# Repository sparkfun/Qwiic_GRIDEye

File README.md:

SparkFun Qwiic Panasonic Grid-EYE Infrared Array AMG88xx
========================================

[*SparkFun Grid-EYE Infrared Array Breakout - AMG8833 (Qwiic) (SEN-14607)*](https://www.sparkfun.com/products/14607)

The GridEYE from Panasonic is a 8 by 8 thermopile array. This means you have an array of 64 pixels each capable of detecting temperature remotely. It’s like having thermal camera (or Predator’s vision) just in really low resolution. The SparkFun Grid-EYE Qwiic carrier board utilizes the high performance, high gain 3.3V AMG88 sensor. Do not hook 5V to this beast! Better yet, use the Qwiic system - it makes it much easier and quicker to get started.

The SparkFun carrier board incorporates all the needed passive components as well as a jumper to change the I2C address and a jumper to remove the pull up resistors if needed.

Repository Contents
-------------------

* **/Documents** - Datasheets
* **/Hardware** - Eagle design files (.brd, .sch)

Documentation
--------------
* **[Arduino Library](https://github.com/sparkfun/SparkFun_GridEYE_Arduino_Library)** - Library for reading the sensor and outputing fun graphics over the serial port
* **[Hookup Guide](https://learn.sparkfun.com/tutorials/qwiic-grid-eye-infrared-array-amg88xx-hookup-guide)** - Basic hookup guide for the Qwiic GRID-Eye Infrared Array.

Product Versions
----------------
* [SEN-14607](https://www.sparkfun.com/products/14607)- SparkFun breakout board for Grid-EYE AMG8833
* [SPX-14568](https://www.sparkfun.com/products/14568)- SparkX breakout board for Grid-EYE AMG8833

License Information
-------------------

This product is _**open source**_! 

Please review the LICENSE.md file for license information. 

If you have any questions or concerns on licensing, please contact techsupport@sparkfun.com.

Please use, reuse, and modify these files as you see fit. Please maintain attribution to SparkFun Electronics and release anyThing Development Board derivative under the same license.

Distributed as-is; no warranty is given.

- Your friends at SparkFun.

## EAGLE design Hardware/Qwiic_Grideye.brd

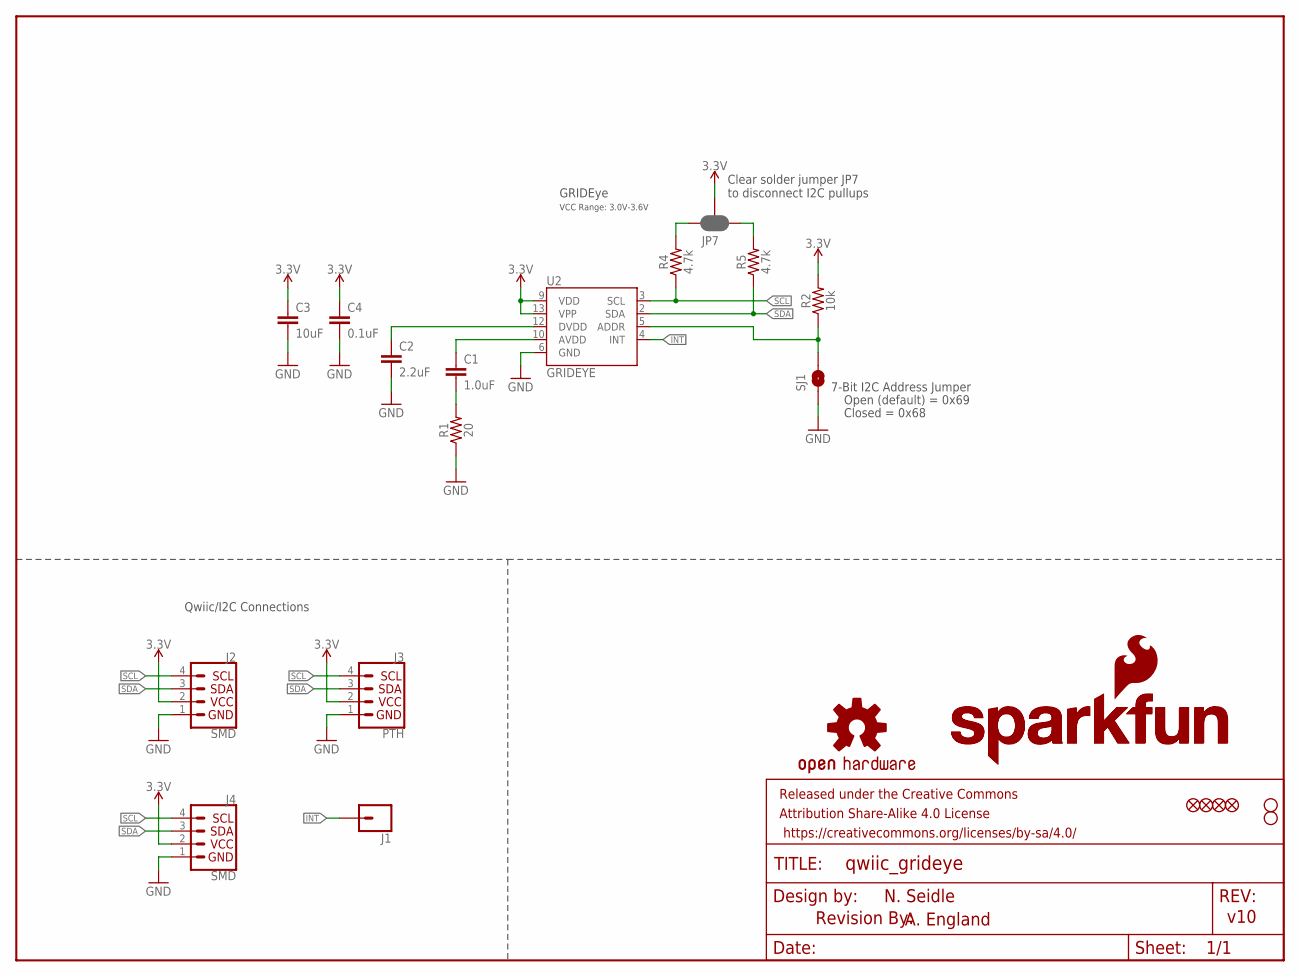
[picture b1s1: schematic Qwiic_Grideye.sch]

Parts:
C1: 1.0uF; 0603
C2: 2.2uF; 0603
C3: 10uF; 0603
C4: 0.1uF; 0603
FRAME1: FRAME-LETTER; CREATIVE_COMMONS
J1: CONN_01PTH_NO_SILK_YES_STOP; 1X01_NO_SILK
J2, J4: SMD; 1X04_1MM_RA
J3: PTH; 1X04_NO_SILK
JP1, JP2, JP5, JP6: FIDUCIALUFIDUCIAL; MICRO-FIDUCIAL
JP3, JP4: STAND-OFF
JP7: JUMPER-SMT_3_2-NC_PASTE_SILK; SMT-JUMPER_3_2-NC_PASTE_SILK
LOGO1: OSHW-LOGOMINI; OSHW-LOGO-MINI
LOGO2: REVISION
R1: 20; 0603
R2: 10k; 0603
R4, R5: 4.7k; 0603
SJ1: SOLDERJUMPERNO; SJ_2S-NO
U2: GRIDEYE; GRIDEYE-AMG88
U$1: SFE_LOGO_NAME.1_INCH; SFE_LOGO_NAME_.1
U$2: SFE_LOGO_NAME_FLAME.1_INCH; SFE_LOGO_NAME_FLAME_.1

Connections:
3.3V: C3.1, C4.1, J2.2 (VCC), J3.2 (VCC), J4.2 (VCC), JP7.2, R2.2, U2.9 (VDD), U2.13 (VPP)
ADDR: R2.1, SJ1.2, U2.5 (ADDR)
GND: C2.2, C3.2, C4.2, J2.1 (GND), J3.1 (GND), J4.1 (GND), R1.1, SJ1.1, U2.6 (GND)
INT: J1.1, U2.4 (INT)
unnamed: JP7.1, R5.2
unnamed: JP7.3, R4.2
unnamed: C2.1, U2.12 (DVDD)
unnamed: C1.1, U2.10 (AVDD)
unnamed: C1.2, R1.2
SCL: J2.4 (SCL), J3.4 (SCL), J4.4 (SCL), R4.1, U2.3 (SCL)
SDA: J2.3 (SDA), J3.3 (SDA), J4.3 (SDA), R5.1, U2.2 (SDA)

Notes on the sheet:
7-Bit I2C Address Jumper
Closed = 0x68
Open (default) = 0x69
N. Seidle
v10
GRIDEye
Clear solder jumper JP7 to disconnect I2C pullups
Qwiic/I2C Connections
A. England
VCC Range: 3.0V-3.6V

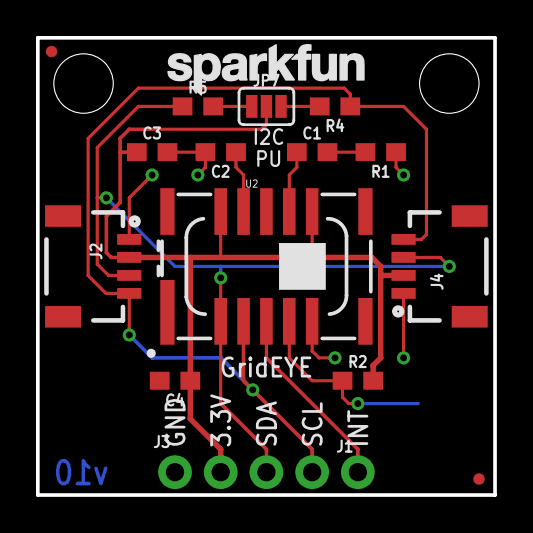
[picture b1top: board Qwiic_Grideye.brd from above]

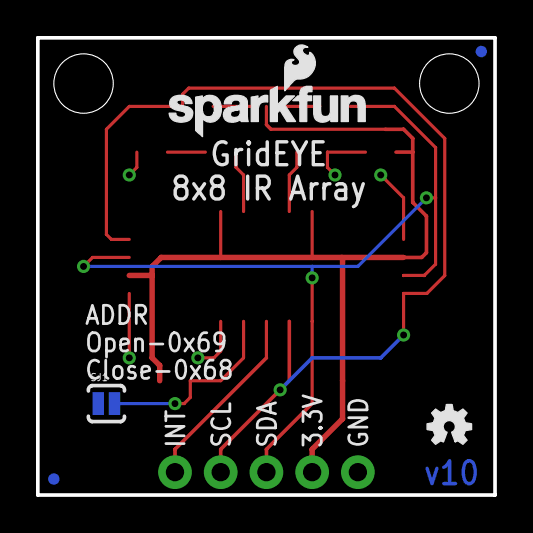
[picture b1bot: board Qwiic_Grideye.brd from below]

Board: 2 copper layers, 25.4 x 25.4 mm, 26 parts (5 on the bottom side), 11 nets.

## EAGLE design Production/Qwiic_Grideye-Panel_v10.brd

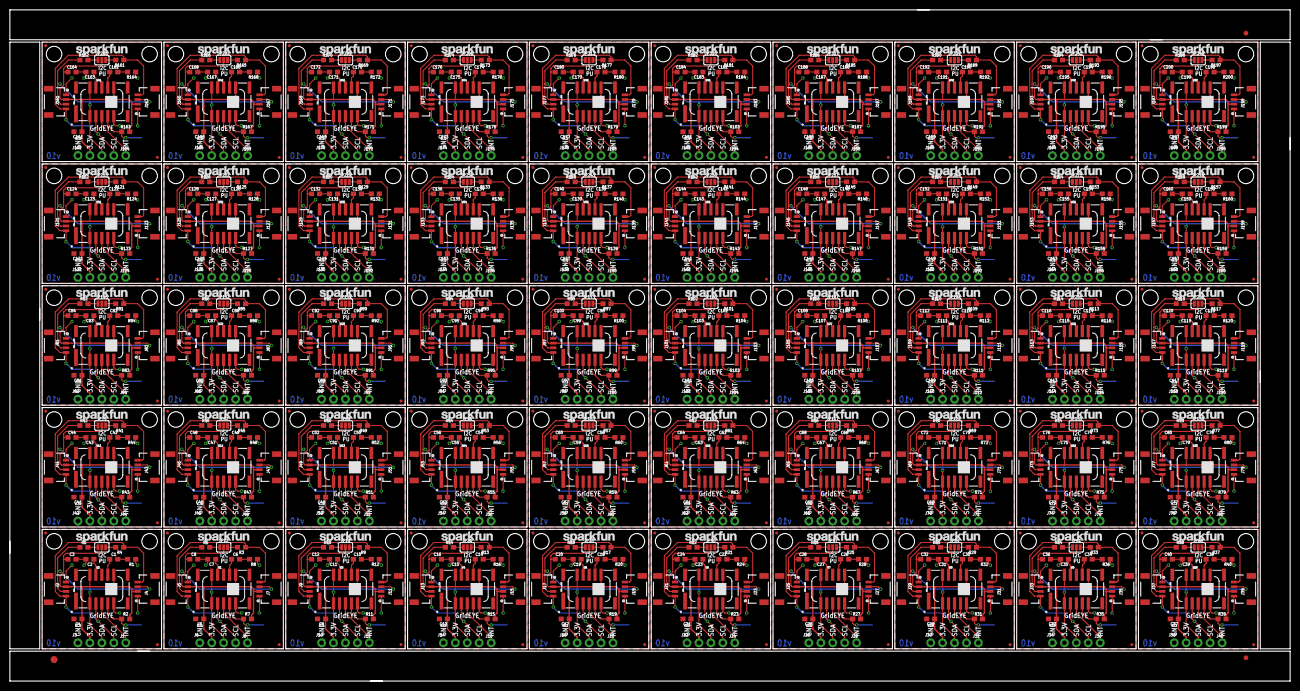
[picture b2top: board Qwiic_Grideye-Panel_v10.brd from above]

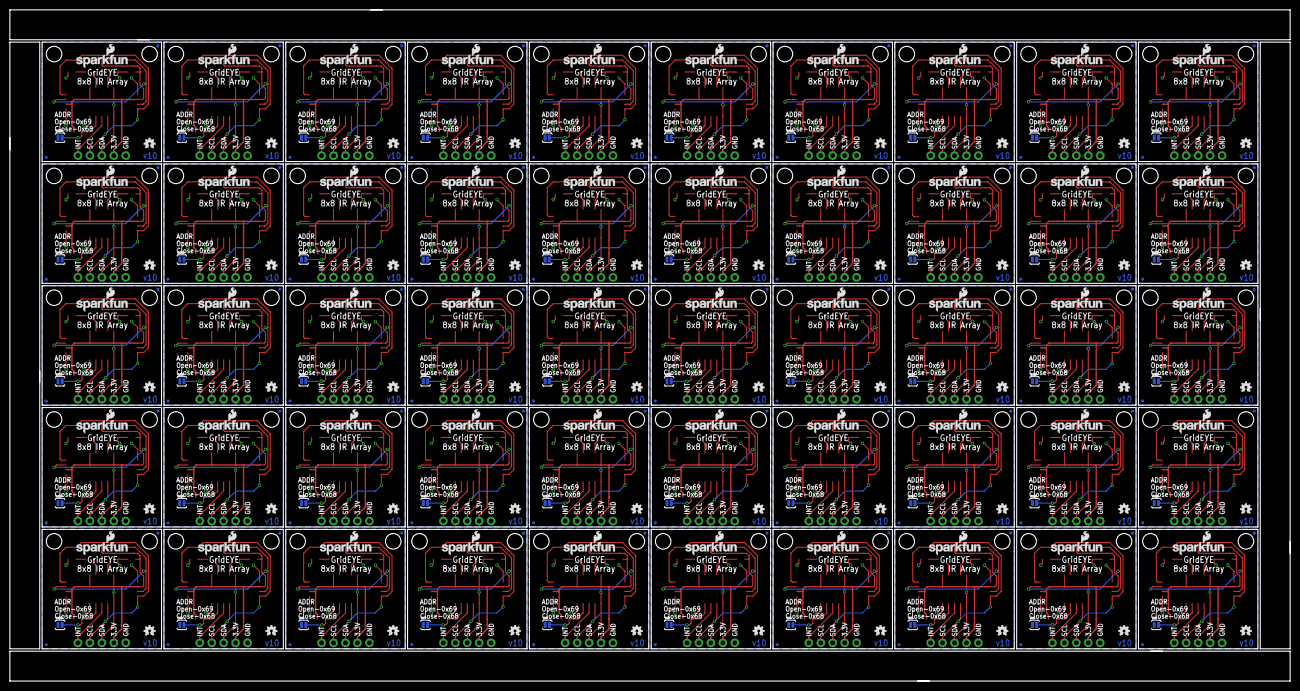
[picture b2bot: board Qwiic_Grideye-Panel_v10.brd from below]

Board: 2 copper layers, 272.3 x 142.7 mm, 1203 parts (250 on the bottom side), 550 nets.

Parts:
C1, C6, C10, C14, C18, C22, C26, C30, C34, C38, C42, C46, C50, C54, C58, C62, C66, C70, C74, C78, C82, C86, C90, C94, C98, C102, C106, C110, C114, C118, C122, C126, C130, C134, C138, C142, C146, C150, C154, C158, C162, C166, C170, C174, C178, C182, C186, C190, C194, C198: 1.0uF; 0603
C2, C7, C11, C15, C19, C23, C27, C31, C35, C39, C43, C47, C51, C55, C59, C63, C67, C71, C75, C79, C83, C87, C91, C95, C99, C103, C107, C111, C115, C119, C123, C127, C131, C135, C139, C143, C147, C151, C155, C159, C163, C167, C171, C175, C179, C183, C187, C191, C195, C199: 2.2uF; 0603
C3, C8, C12, C16, C20, C24, C28, C32, C36, C40, C44, C48, C52, C56, C60, C64, C68, C72, C76, C80, C84, C88, C92, C96, C100, C104, C108, C112, C116, C120, C124, C128, C132, C136, C140, C144, C148, C152, C156, C160, C164, C168, C172, C176, C180, C184, C188, C192, C196, C200: 10uF; 0603
C4, C5, C9, C13, C17, C21, C25, C29, C33, C37, C41, C45, C49, C53, C57, C61, C65, C69, C73, C77, C81, C85, C89, C93, C97, C101, C105, C109, C113, C117, C121, C125, C129, C133, C137, C141, C145, C149, C153, C157, C161, C165, C169, C173, C177, C181, C185, C189, C193, C197: 0.1uF; 0603
E$1: FIDUCIAL-1.5X3
E$5, E$8: FIDUCIAL-1X2
J1, J8, J12, J16, J20, J24, J28, J32, J36, J40, J44, J48, J52, J56, J60, J64, J68, J72, J76, J80, J84, J88, J92, J96, J100, J104, J108, J112, J116, J120, J124, J128, J132, J136, J140, J144, J148, J152, J156, J160, J164, J168, J172, J176, J180, J184, J188, J192, J196, J200: 1X01_NO_SILK
J2, J4, J5, J7, J9, J11, J13, J15, J17, J19, J21, J23, J25, J27, J29, J31, J33, J35, J37, J39, J41, J43, J45, J47, J49, J51, J53, J55, J57, J59, J61, J63, J65, J67, J69, J71, J73, J75, J77, J79, J81, J83, J85, J87, J89, J91, J93, J95, J97, J99, J101, J103, J105, J107, J109, J111, J113, J115, J117, J119, J121, J123, J125, J127, J129, J131, J133, J135, J137, J139, J141, J143, J145, J147, J149, J151, J153, J155, J157, J159, J161, J163, J165, J167, J169, J171, J173, J175, J177, J179, J181, J183, J185, J187, J189, J191, J193, J195, J197, J199: SMD; 1X04_1MM_RA
J3, J6, J10, J14, J18, J22, J26, J30, J34, J38, J42, J46, J50, J54, J58, J62, J66, J70, J74, J78, J82, J86, J90, J94, J98, J102, J106, J110, J114, J118, J122, J126, J130, J134, J138, J142, J146, J150, J154, J158, J162, J166, J170, J174, J178, J182, J186, J190, J194, J198: PTH; 1X04_NO_SILK
JP1, JP2, JP5, JP6, JP10, JP11, JP13, JP14, JP17, JP18, JP20, JP21, JP24, JP25, JP27, JP28, JP31, JP32, JP34, JP35, JP38, JP39, JP41, JP42, JP45, JP46, JP48, JP49, JP52, JP53, JP55, JP56, JP59, JP60, JP62, JP63, JP66, JP67, JP69, JP70, JP73, JP74, JP76, JP77, JP80, JP81, JP83, JP84, JP87, JP88, JP90, JP91, JP94, JP95, JP97, JP98, JP101, JP102, JP104, JP105, JP108, JP109, JP111, JP112, JP115, JP116, JP118, JP119, JP122, JP123, JP125, JP126, JP129, JP130, JP132, JP133, JP136, JP137, JP139, JP140, JP143, JP144, JP146, JP147, JP150, JP151, JP153, JP154, JP157, JP158, JP160, JP161, JP164, JP165, JP167, JP168, JP171, JP172, JP174, JP175, JP178, JP179, JP181, JP182, JP185, JP186, JP188, JP189, JP192, JP193, JP195, JP196, JP199, JP200, JP202, JP203, JP206, JP207, JP209, JP210, JP213, JP214, JP216, JP217, JP220, JP221, JP223, JP224, JP227, JP228, JP230, JP231, JP234, JP235, JP237, JP238, JP241, JP242, JP244, JP245, JP248, JP249, JP251, JP252, JP255, JP256, JP258, JP259, JP262, JP263, JP265, JP266, JP269, JP270, JP272, JP273, JP276, JP277, JP279, JP280, JP283, JP284, JP286, JP287, JP290, JP291, JP293, JP294, JP297, JP298, JP300, JP301, JP304, JP305, JP307, JP308, JP311, JP312, JP314, JP315, JP318, JP319, JP321, JP322, JP325, JP326, JP328, JP329, JP332, JP333, JP335, JP336, JP339, JP340, JP342, JP343, JP346, JP347, JP349, JP350: FIDUCIALUFIDUCIAL; MICRO-FIDUCIAL
JP3, JP4, JP8, JP9, JP15, JP16, JP22, JP23, JP29, JP30, JP36, JP37, JP43, JP44, JP50, JP51, JP57, JP58, JP64, JP65, JP71, JP72, JP78, JP79, JP85, JP86, JP92, JP93, JP99, JP100, JP106, JP107, JP113, JP114, JP120, JP121, JP127, JP128, JP134, JP135, JP141, JP142, JP148, JP149, JP155, JP156, JP162, JP163, JP169, JP170, JP176, JP177, JP183, JP184, JP190, JP191, JP197, JP198, JP204, JP205, JP211, JP212, JP218, JP219, JP225, JP226, JP232, JP233, JP239, JP240, JP246, JP247, JP253, JP254, JP260, JP261, JP267, JP268, JP274, JP275, JP281, JP282, JP288, JP289, JP295, JP296, JP302, JP303, JP309, JP310, JP316, JP317, JP323, JP324, JP330, JP331, JP337, JP338, JP344, JP345: STAND-OFF
JP7, JP12, JP19, JP26, JP33, JP40, JP47, JP54, JP61, JP68, JP75, JP82, JP89, JP96, JP103, JP110, JP117, JP124, JP131, JP138, JP145, JP152, JP159, JP166, JP173, JP180, JP187, JP194, JP201, JP208, JP215, JP222, JP229, JP236, JP243, JP250, JP257, JP264, JP271, JP278, JP285, JP292, JP299, JP306, JP313, JP320, JP327, JP334, JP341, JP348: SMT-JUMPER_3_2-NC_PASTE_SILK
LOGO1, LOGO2, LOGO3, LOGO4, LOGO5, LOGO6, LOGO7, LOGO8, LOGO9, LOGO10, LOGO11, LOGO12, LOGO13, LOGO14, LOGO15, LOGO16, LOGO17, LOGO18, LOGO19, LOGO20, LOGO21, LOGO22, LOGO23, LOGO24, LOGO25, LOGO26, LOGO27, LOGO28, LOGO29, LOGO30, LOGO31, LOGO32, LOGO33, LOGO34, LOGO35, LOGO36, LOGO37, LOGO38, LOGO39, LOGO40, LOGO41, LOGO42, LOGO43, LOGO44, LOGO45, LOGO46, LOGO47, LOGO48, LOGO49, LOGO50: OSHW-LOGOMINI; OSHW-LOGO-MINI
R1, R8, R12, R16, R20, R24, R28, R32, R36, R40, R44, R48, R52, R56, R60, R64, R68, R72, R76, R80, R84, R88, R92, R96, R100, R104, R108, R112, R116, R120, R124, R128, R132, R136, R140, R144, R148, R152, R156, R160, R164, R168, R172, R176, R180, R184, R188, R192, R196, R200: 20; 0603
R2, R7, R11, R15, R19, R23, R27, R31, R35, R39, R43, R47, R51, R55, R59, R63, R67, R71, R75, R79, R83, R87, R91, R95, R99, R103, R107, R111, R115, R119, R123, R127, R131, R135, R139, R143, R147, R151, R155, R159, R163, R167, R171, R175, R179, R183, R187, R191, R195, R199: 10k; 0603
R3, R4, R5, R6, R9, R10, R13, R14, R17, R18, R21, R22, R25, R26, R29, R30, R33, R34, R37, R38, R41, R42, R45, R46, R49, R50, R53, R54, R57, R58, R61, R62, R65, R66, R69, R70, R73, R74, R77, R78, R81, R82, R85, R86, R89, R90, R93, R94, R97, R98, R101, R102, R105, R106, R109, R110, R113, R114, R117, R118, R121, R122, R125, R126, R129, R130, R133, R134, R137, R138, R141, R142, R145, R146, R149, R150, R153, R154, R157, R158, R161, R162, R165, R166, R169, R170, R173, R174, R177, R178, R181, R182, R185, R186, R189, R190, R193, R194, R197, R198: 4.7k; 0603
SJ1, SJ2, SJ3, SJ4, SJ5, SJ6, SJ7, SJ8, SJ9, SJ10, SJ11, SJ12, SJ13, SJ14, SJ15, SJ16, SJ17, SJ18, SJ19, SJ20, SJ21, SJ22, SJ23, SJ24, SJ25, SJ26, SJ27, SJ28, SJ29, SJ30, SJ31, SJ32, SJ33, SJ34, SJ35, SJ36, SJ37, SJ38, SJ39, SJ40, SJ41, SJ42, SJ43, SJ44, SJ45, SJ46, SJ47, SJ48, SJ49, SJ50: SJ_2S-NO
U1, U2, U3, U4, U5, U6, U7, U8, U9, U10, U11, U12, U13, U14, U15, U16, U17, U18, U19, U20, U21, U22, U23, U24, U25, U26, U27, U28, U29, U30, U31, U32, U33, U34, U35, U36, U37, U38, U39, U40, U41, U42, U43, U44, U45, U46, U47, U48, U49, U50: GRIDEYE; GRIDEYE-AMG88
U$1, U$4, U$6, U$8, U$10, U$12, U$14, U$16, U$18, U$20, U$22, U$24, U$26, U$28, U$30, U$32, U$34, U$36, U$38, U$40, U$42, U$44, U$46, U$48, U$50, U$52, U$54, U$56, U$58, U$60, U$62, U$64, U$66, U$68, U$70, U$72, U$74, U$76, U$78, U$80, U$82, U$84, U$86, U$88, U$90, U$92, U$94, U$96, U$98, U$100: SFE_LOGO_NAME.1_INCH; SFE_LOGO_NAME_.1
U$2, U$3, U$5, U$7, U$9, U$11, U$13, U$15, U$17, U$19, U$21, U$23, U$25, U$27, U$29, U$31, U$33, U$35, U$37, U$39, U$41, U$43, U$45, U$47, U$49, U$51, U$53, U$55, U$57, U$59, U$61, U$63, U$65, U$67, U$69, U$71, U$73, U$75, U$77, U$79, U$81, U$83, U$85, U$87, U$89, U$91, U$93, U$95, U$97, U$99: SFE_LOGO_NAME_FLAME.1_INCH; SFE_LOGO_NAME_FLAME_.1

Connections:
3.3V: C3.1, C4.1, J2.2, J3.2, J4.2, JP7.2, R2.2, U2.9, U2.13
3.3V1: C5.1, C8.1, J5.2, J6.2, J7.2, JP12.2, R7.2, U1.9, U1.13
3.3V2: C9.1, C12.1, J9.2, J10.2, J11.2, JP19.2, R11.2, U3.9, U3.13
3.3V3: C13.1, C16.1, J13.2, J14.2, J15.2, JP26.2, R15.2, U4.9, U4.13
3.3V4: C17.1, C20.1, J17.2, J18.2, J19.2, JP33.2, R19.2, U5.9, U5.13
3.3V5: C21.1, C24.1, J21.2, J22.2, J23.2, JP40.2, R23.2, U6.9, U6.13
3.3V6: C25.1, C28.1, J25.2, J26.2, J27.2, JP47.2, R27.2, U7.9, U7.13
3.3V7: C29.1, C32.1, J29.2, J30.2, J31.2, JP54.2, R31.2, U8.9, U8.13
3.3V8: C33.1, C36.1, J33.2, J34.2, J35.2, JP61.2, R35.2, U9.9, U9.13
3.3V9: C37.1, C40.1, J37.2, J38.2, J39.2, JP68.2, R39.2, U10.9, U10.13
3.3V10: C41.1, C44.1, J41.2, J42.2, J43.2, JP75.2, R43.2, U11.9, U11.13
3.3V11: C45.1, C48.1, J45.2, J46.2, J47.2, JP82.2, R47.2, U12.9, U12.13
3.3V12: C49.1, C52.1, J49.2, J50.2, J51.2, JP89.2, R51.2, U13.9, U13.13
3.3V13: C53.1, C56.1, J53.2, J54.2, J55.2, JP96.2, R55.2, U14.9, U14.13
3.3V14: C57.1, C60.1, J57.2, J58.2, J59.2, JP103.2, R59.2, U15.9, U15.13
3.3V15: C61.1, C64.1, J61.2, J62.2, J63.2, JP110.2, R63.2, U16.9, U16.13
3.3V16: C65.1, C68.1, J65.2, J66.2, J67.2, JP117.2, R67.2, U17.9, U17.13
3.3V17: C69.1, C72.1, J69.2, J70.2, J71.2, JP124.2, R71.2, U18.9, U18.13
3.3V18: C73.1, C76.1, J73.2, J74.2, J75.2, JP131.2, R75.2, U19.9, U19.13
3.3V19: C77.1, C80.1, J77.2, J78.2, J79.2, JP138.2, R79.2, U20.9, U20.13
3.3V20: C81.1, C84.1, J81.2, J82.2, J83.2, JP145.2, R83.2, U21.9, U21.13
3.3V21: C85.1, C88.1, J85.2, J86.2, J87.2, JP152.2, R87.2, U22.9, U22.13
3.3V22: C89.1, C92.1, J89.2, J90.2, J91.2, JP159.2, R91.2, U23.9, U23.13
3.3V23: C93.1, C96.1, J93.2, J94.2, J95.2, JP166.2, R95.2, U24.9, U24.13
3.3V24: C97.1, C100.1, J97.2, J98.2, J99.2, JP173.2, R99.2, U25.9, U25.13
3.3V25: C101.1, C104.1, J101.2, J102.2, J103.2, JP180.2, R103.2, U26.9, U26.13
3.3V26: C105.1, C108.1, J105.2, J106.2, J107.2, JP187.2, R107.2, U27.9, U27.13
3.3V27: C109.1, C112.1, J109.2, J110.2, J111.2, JP194.2, R111.2, U28.9, U28.13
3.3V28: C113.1, C116.1, J113.2, J114.2, J115.2, JP201.2, R115.2, U29.9, U29.13
3.3V29: C117.1, C120.1, J117.2, J118.2, J119.2, JP208.2, R119.2, U30.9, U30.13
3.3V30: C121.1, C124.1, J121.2, J122.2, J123.2, JP215.2, R123.2, U31.9, U31.13
3.3V31: C125.1, C128.1, J125.2, J126.2, J127.2, JP222.2, R127.2, U32.9, U32.13
3.3V32: C129.1, C132.1, J129.2, J130.2, J131.2, JP229.2, R131.2, U33.9, U33.13
3.3V33: C133.1, C136.1, J133.2, J134.2, J135.2, JP236.2, R135.2, U34.9, U34.13
3.3V34: C137.1, C140.1, J137.2, J138.2, J139.2, JP243.2, R139.2, U35.9, U35.13
3.3V35: C141.1, C144.1, J141.2, J142.2, J143.2, JP250.2, R143.2, U36.9, U36.13
3.3V36: C145.1, C148.1, J145.2, J146.2, J147.2, JP257.2, R147.2, U37.9, U37.13
3.3V37: C149.1, C152.1, J149.2, J150.2, J151.2, JP264.2, R151.2, U38.9, U38.13
3.3V38: C153.1, C156.1, J153.2, J154.2, J155.2, JP271.2, R155.2, U39.9, U39.13
3.3V39: C157.1, C160.1, J157.2, J158.2, J159.2, JP278.2, R159.2, U40.9, U40.13
3.3V40: C161.1, C164.1, J161.2, J162.2, J163.2, JP285.2, R163.2, U41.9, U41.13
3.3V41: C165.1, C168.1, J165.2, J166.2, J167.2, JP292.2, R167.2, U42.9, U42.13
3.3V42: C169.1, C172.1, J169.2, J170.2, J171.2, JP299.2, R171.2, U43.9, U43.13
3.3V43: C173.1, C176.1, J173.2, J174.2, J175.2, JP306.2, R175.2, U44.9, U44.13
3.3V44: C177.1, C180.1, J177.2, J178.2, J179.2, JP313.2, R179.2, U45.9, U45.13
3.3V45: C181.1, C184.1, J181.2, J182.2, J183.2, JP320.2, R183.2, U46.9, U46.13
3.3V46: C185.1, C188.1, J185.2, J186.2, J187.2, JP327.2, R187.2, U47.9, U47.13
3.3V47: C189.1, C192.1, J189.2, J190.2, J191.2, JP334.2, R191.2, U48.9, U48.13
3.3V48: C193.1, C196.1, J193.2, J194.2, J195.2, JP341.2, R195.2, U49.9, U49.13
3.3V49: C197.1, C200.1, J197.2, J198.2, J199.2, JP348.2, R199.2, U50.9, U50.13
ADDR: R2.1, SJ1.2, U2.5
ADDR1: R7.1, SJ2.2, U1.5
ADDR2: R11.1, SJ3.2, U3.5
ADDR3: R15.1, SJ4.2, U4.5
ADDR4: R19.1, SJ5.2, U5.5
ADDR5: R23.1, SJ6.2, U6.5
ADDR6: R27.1, SJ7.2, U7.5
ADDR7: R31.1, SJ8.2, U8.5
ADDR8: R35.1, SJ9.2, U9.5
ADDR9: R39.1, SJ10.2, U10.5
ADDR10: R43.1, SJ11.2, U11.5
ADDR11: R47.1, SJ12.2, U12.5
ADDR12: R51.1, SJ13.2, U13.5
ADDR13: R55.1, SJ14.2, U14.5
ADDR14: R59.1, SJ15.2, U15.5
ADDR15: R63.1, SJ16.2, U16.5
ADDR16: R67.1, SJ17.2, U17.5
ADDR17: R71.1, SJ18.2, U18.5
ADDR18: R75.1, SJ19.2, U19.5
ADDR19: R79.1, SJ20.2, U20.5
ADDR20: R83.1, SJ21.2, U21.5
ADDR21: R87.1, SJ22.2, U22.5
ADDR22: R91.1, SJ23.2, U23.5
ADDR23: R95.1, SJ24.2, U24.5
ADDR24: R99.1, SJ25.2, U25.5
ADDR25: R103.1, SJ26.2, U26.5
ADDR26: R107.1, SJ27.2, U27.5
ADDR27: R111.1, SJ28.2, U28.5
ADDR28: R115.1, SJ29.2, U29.5
ADDR29: R119.1, SJ30.2, U30.5
ADDR30: R123.1, SJ31.2, U31.5
ADDR31: R127.1, SJ32.2, U32.5
ADDR32: R131.1, SJ33.2, U33.5
ADDR33: R135.1, SJ34.2, U34.5
ADDR34: R139.1, SJ35.2, U35.5
ADDR35: R143.1, SJ36.2, U36.5
ADDR36: R147.1, SJ37.2, U37.5
ADDR37: R151.1, SJ38.2, U38.5
ADDR38: R155.1, SJ39.2, U39.5
ADDR39: R159.1, SJ40.2, U40.5
ADDR40: R163.1, SJ41.2, U41.5
ADDR41: R167.1, SJ42.2, U42.5
ADDR42: R171.1, SJ43.2, U43.5
ADDR43: R175.1, SJ44.2, U44.5
ADDR44: R179.1, SJ45.2, U45.5
ADDR45: R183.1, SJ46.2, U46.5
ADDR46: R187.1, SJ47.2, U47.5
ADDR47: R191.1, SJ48.2, U48.5
ADDR48: R195.1, SJ49.2, U49.5
ADDR49: R199.1, SJ50.2, U50.5
GND: C2.2, C3.2, C4.2, J2.1, J3.1, J4.1, R1.1, SJ1.1, U2.6
GND1: C5.2, C7.2, C8.2, J5.1, J6.1, J7.1, R8.1, SJ2.1, U1.6
GND2: C9.2, C11.2, C12.2, J9.1, J10.1, J11.1, R12.1, SJ3.1, U3.6
GND3: C13.2, C15.2, C16.2, J13.1, J14.1, J15.1, R16.1, SJ4.1, U4.6
GND4: C17.2, C19.2, C20.2, J17.1, J18.1, J19.1, R20.1, SJ5.1, U5.6
GND5: C21.2, C23.2, C24.2, J21.1, J22.1, J23.1, R24.1, SJ6.1, U6.6
GND6: C25.2, C27.2, C28.2, J25.1, J26.1, J27.1, R28.1, SJ7.1, U7.6
GND7: C29.2, C31.2, C32.2, J29.1, J30.1, J31.1, R32.1, SJ8.1, U8.6
GND8: C33.2, C35.2, C36.2, J33.1, J34.1, J35.1, R36.1, SJ9.1, U9.6
GND9: C37.2, C39.2, C40.2, J37.1, J38.1, J39.1, R40.1, SJ10.1, U10.6
GND10: C41.2, C43.2, C44.2, J41.1, J42.1, J43.1, R44.1, SJ11.1, U11.6
GND11: C45.2, C47.2, C48.2, J45.1, J46.1, J47.1, R48.1, SJ12.1, U12.6
GND12: C49.2, C51.2, C52.2, J49.1, J50.1, J51.1, R52.1, SJ13.1, U13.6
GND13: C53.2, C55.2, C56.2, J53.1, J54.1, J55.1, R56.1, SJ14.1, U14.6
GND14: C57.2, C59.2, C60.2, J57.1, J58.1, J59.1, R60.1, SJ15.1, U15.6
GND15: C61.2, C63.2, C64.2, J61.1, J62.1, J63.1, R64.1, SJ16.1, U16.6
GND16: C65.2, C67.2, C68.2, J65.1, J66.1, J67.1, R68.1, SJ17.1, U17.6
GND17: C69.2, C71.2, C72.2, J69.1, J70.1, J71.1, R72.1, SJ18.1, U18.6
GND18: C73.2, C75.2, C76.2, J73.1, J74.1, J75.1, R76.1, SJ19.1, U19.6
GND19: C77.2, C79.2, C80.2, J77.1, J78.1, J79.1, R80.1, SJ20.1, U20.6
GND20: C81.2, C83.2, C84.2, J81.1, J82.1, J83.1, R84.1, SJ21.1, U21.6
GND21: C85.2, C87.2, C88.2, J85.1, J86.1, J87.1, R88.1, SJ22.1, U22.6
GND22: C89.2, C91.2, C92.2, J89.1, J90.1, J91.1, R92.1, SJ23.1, U23.6
GND23: C93.2, C95.2, C96.2, J93.1, J94.1, J95.1, R96.1, SJ24.1, U24.6
GND24: C97.2, C99.2, C100.2, J97.1, J98.1, J99.1, R100.1, SJ25.1, U25.6
GND25: C101.2, C103.2, C104.2, J101.1, J102.1, J103.1, R104.1, SJ26.1, U26.6
GND26: C105.2, C107.2, C108.2, J105.1, J106.1, J107.1, R108.1, SJ27.1, U27.6
GND27: C109.2, C111.2, C112.2, J109.1, J110.1, J111.1, R112.1, SJ28.1, U28.6
GND28: C113.2, C115.2, C116.2, J113.1, J114.1, J115.1, R116.1, SJ29.1, U29.6
GND29: C117.2, C119.2, C120.2, J117.1, J118.1, J119.1, R120.1, SJ30.1, U30.6
GND30: C121.2, C123.2, C124.2, J121.1, J122.1, J123.1, R124.1, SJ31.1, U31.6
GND31: C125.2, C127.2, C128.2, J125.1, J126.1, J127.1, R128.1, SJ32.1, U32.6
GND32: C129.2, C131.2, C132.2, J129.1, J130.1, J131.1, R132.1, SJ33.1, U33.6
GND33: C133.2, C135.2, C136.2, J133.1, J134.1, J135.1, R136.1, SJ34.1, U34.6
GND34: C137.2, C139.2, C140.2, J137.1, J138.1, J139.1, R140.1, SJ35.1, U35.6
GND35: C141.2, C143.2, C144.2, J141.1, J142.1, J143.1, R144.1, SJ36.1, U36.6
GND36: C145.2, C147.2, C148.2, J145.1, J146.1, J147.1, R148.1, SJ37.1, U37.6
GND37: C149.2, C151.2, C152.2, J149.1, J150.1, J151.1, R152.1, SJ38.1, U38.6
GND38: C153.2, C155.2, C156.2, J153.1, J154.1, J155.1, R156.1, SJ39.1, U39.6
GND39: C157.2, C159.2, C160.2, J157.1, J158.1, J159.1, R160.1, SJ40.1, U40.6
GND40: C161.2, C163.2, C164.2, J161.1, J162.1, J163.1, R164.1, SJ41.1, U41.6
GND41: C165.2, C167.2, C168.2, J165.1, J166.1, J167.1, R168.1, SJ42.1, U42.6
GND42: C169.2, C171.2, C172.2, J169.1, J170.1, J171.1, R172.1, SJ43.1, U43.6
GND43: C173.2, C175.2, C176.2, J173.1, J174.1, J175.1, R176.1, SJ44.1, U44.6
GND44: C177.2, C179.2, C180.2, J177.1, J178.1, J179.1, R180.1, SJ45.1, U45.6
GND45: C181.2, C183.2, C184.2, J181.1, J182.1, J183.1, R184.1, SJ46.1, U46.6
GND46: C185.2, C187.2, C188.2, J185.1, J186.1, J187.1, R188.1, SJ47.1, U47.6
GND47: C189.2, C191.2, C192.2, J189.1, J190.1, J191.1, R192.1, SJ48.1, U48.6
GND48: C193.2, C195.2, C196.2, J193.1, J194.1, J195.1, R196.1, SJ49.1, U49.6
GND49: C197.2, C199.2, C200.2, J197.1, J198.1, J199.1, R200.1, SJ50.1, U50.6
INT: J1.1, U2.4
INT1: J8.1, U1.4
INT2: J12.1, U3.4
INT3: J16.1, U4.4
INT4: J20.1, U5.4
INT5: J24.1, U6.4
INT6: J28.1, U7.4
INT7: J32.1, U8.4
INT8: J36.1, U9.4
INT9: J40.1, U10.4
INT10: J44.1, U11.4
INT11: J48.1, U12.4
INT12: J52.1, U13.4
INT13: J56.1, U14.4
INT14: J60.1, U15.4
INT15: J64.1, U16.4
INT16: J68.1, U17.4
INT17: J72.1, U18.4
INT18: J76.1, U19.4
INT19: J80.1, U20.4
INT20: J84.1, U21.4
INT21: J88.1, U22.4
INT22: J92.1, U23.4
INT23: J96.1, U24.4
INT24: J100.1, U25.4
INT25: J104.1, U26.4
INT26: J108.1, U27.4
INT27: J112.1, U28.4
INT28: J116.1, U29.4
INT29: J120.1, U30.4
INT30: J124.1, U31.4
INT31: J128.1, U32.4
INT32: J132.1, U33.4
INT33: J136.1, U34.4
INT34: J140.1, U35.4
INT35: J144.1, U36.4
INT36: J148.1, U37.4
INT37: J152.1, U38.4
INT38: J156.1, U39.4
INT39: J160.1, U40.4
INT40: J164.1, U41.4
INT41: J168.1, U42.4
INT42: J172.1, U43.4
INT43: J176.1, U44.4
INT44: J180.1, U45.4
INT45: J184.1, U46.4
INT46: J188.1, U47.4
INT47: J192.1, U48.4
INT48: J196.1, U49.4
INT49: J200.1, U50.4
unnamed: JP7.1, R5.2
unnamed: JP7.3, R4.2
unnamed: C2.1, U2.12
unnamed: C1.1, U2.10
unnamed: C1.2, R1.2
unnamed: JP12.1, R6.2
unnamed: JP12.3, R3.2
unnamed: C7.1, U1.12
unnamed: C6.1, U1.10
unnamed: C6.2, R8.2
unnamed: JP19.1, R10.2
unnamed: JP19.3, R9.2
unnamed: C11.1, U3.12
unnamed: C10.1, U3.10
unnamed: C10.2, R12.2
unnamed: JP26.1, R14.2
unnamed: JP26.3, R13.2
unnamed: C15.1, U4.12
unnamed: C14.1, U4.10
unnamed: C14.2, R16.2
unnamed: JP33.1, R18.2
unnamed: JP33.3, R17.2
unnamed: C19.1, U5.12
unnamed: C18.1, U5.10
unnamed: C18.2, R20.2
unnamed: JP40.1, R22.2
unnamed: JP40.3, R21.2
unnamed: C23.1, U6.12
unnamed: C22.1, U6.10
unnamed: C22.2, R24.2
unnamed: JP47.1, R26.2
unnamed: JP47.3, R25.2
unnamed: C27.1, U7.12
unnamed: C26.1, U7.10
unnamed: C26.2, R28.2
unnamed: JP54.1, R30.2
unnamed: JP54.3, R29.2
unnamed: C31.1, U8.12
unnamed: C30.1, U8.10
unnamed: C30.2, R32.2
unnamed: JP61.1, R34.2
unnamed: JP61.3, R33.2
unnamed: C35.1, U9.12
unnamed: C34.1, U9.10
unnamed: C34.2, R36.2
unnamed: JP68.1, R38.2
unnamed: JP68.3, R37.2
unnamed: C39.1, U10.12
unnamed: C38.1, U10.10
unnamed: C38.2, R40.2
unnamed: JP75.1, R42.2
unnamed: JP75.3, R41.2
unnamed: C43.1, U11.12
unnamed: C42.1, U11.10
unnamed: C42.2, R44.2
unnamed: JP82.1, R46.2
unnamed: JP82.3, R45.2
unnamed: C47.1, U12.12
unnamed: C46.1, U12.10
unnamed: C46.2, R48.2
unnamed: JP89.1, R50.2
unnamed: JP89.3, R49.2
unnamed: C51.1, U13.12
unnamed: C50.1, U13.10
unnamed: C50.2, R52.2
unnamed: JP96.1, R54.2
unnamed: JP96.3, R53.2
unnamed: C55.1, U14.12
unnamed: C54.1, U14.10
unnamed: C54.2, R56.2
unnamed: JP103.1, R58.2
unnamed: JP103.3, R57.2
unnamed: C59.1, U15.12
unnamed: C58.1, U15.10
unnamed: C58.2, R60.2
unnamed: JP110.1, R62.2
unnamed: JP110.3, R61.2
unnamed: C63.1, U16.12
unnamed: C62.1, U16.10
unnamed: C62.2, R64.2
unnamed: JP117.1, R66.2
unnamed: JP117.3, R65.2
unnamed: C67.1, U17.12
unnamed: C66.1, U17.10
unnamed: C66.2, R68.2
unnamed: JP124.1, R70.2
unnamed: JP124.3, R69.2
unnamed: C71.1, U18.12
unnamed: C70.1, U18.10
unnamed: C70.2, R72.2
unnamed: JP131.1, R74.2
unnamed: JP131.3, R73.2
unnamed: C75.1, U19.12
unnamed: C74.1, U19.10
unnamed: C74.2, R76.2
unnamed: JP138.1, R78.2
unnamed: JP138.3, R77.2
unnamed: C79.1, U20.12
unnamed: C78.1, U20.10
unnamed: C78.2, R80.2
unnamed: JP145.1, R82.2
unnamed: JP145.3, R81.2
unnamed: C83.1, U21.12
unnamed: C82.1, U21.10
unnamed: C82.2, R84.2
unnamed: JP152.1, R86.2
unnamed: JP152.3, R85.2
unnamed: C87.1, U22.12
unnamed: C86.1, U22.10
unnamed: C86.2, R88.2
unnamed: JP159.1, R90.2
unnamed: JP159.3, R89.2
unnamed: C91.1, U23.12
unnamed: C90.1, U23.10
unnamed: C90.2, R92.2
unnamed: JP166.1, R94.2
unnamed: JP166.3, R93.2
unnamed: C95.1, U24.12
unnamed: C94.1, U24.10
unnamed: C94.2, R96.2
unnamed: JP173.1, R98.2
unnamed: JP173.3, R97.2
unnamed: C99.1, U25.12
unnamed: C98.1, U25.10
unnamed: C98.2, R100.2
unnamed: JP180.1, R102.2
unnamed: JP180.3, R101.2
unnamed: C103.1, U26.12
unnamed: C102.1, U26.10
unnamed: C102.2, R104.2
unnamed: JP187.1, R106.2
unnamed: JP187.3, R105.2
unnamed: C107.1, U27.12
unnamed: C106.1, U27.10
unnamed: C106.2, R108.2
unnamed: JP194.1, R110.2
unnamed: JP194.3, R109.2
unnamed: C111.1, U28.12
unnamed: C110.1, U28.10
unnamed: C110.2, R112.2
unnamed: JP201.1, R114.2
unnamed: JP201.3, R113.2
unnamed: C115.1, U29.12
unnamed: C114.1, U29.10
unnamed: C114.2, R116.2
unnamed: JP208.1, R118.2
unnamed: JP208.3, R117.2
unnamed: C119.1, U30.12
unnamed: C118.1, U30.10
unnamed: C118.2, R120.2
unnamed: JP215.1, R122.2
unnamed: JP215.3, R121.2
unnamed: C123.1, U31.12
unnamed: C122.1, U31.10
unnamed: C122.2, R124.2
unnamed: JP222.1, R126.2
unnamed: JP222.3, R125.2
unnamed: C127.1, U32.12
unnamed: C126.1, U32.10
unnamed: C126.2, R128.2
unnamed: JP229.1, R130.2
unnamed: JP229.3, R129.2
unnamed: C131.1, U33.12
unnamed: C130.1, U33.10
unnamed: C130.2, R132.2
unnamed: JP236.1, R134.2
unnamed: JP236.3, R133.2
unnamed: C135.1, U34.12
unnamed: C134.1, U34.10
unnamed: C134.2, R136.2
unnamed: JP243.1, R138.2
unnamed: JP243.3, R137.2
unnamed: C139.1, U35.12
unnamed: C138.1, U35.10
unnamed: C138.2, R140.2
unnamed: JP250.1, R142.2
unnamed: JP250.3, R141.2
unnamed: C143.1, U36.12
unnamed: C142.1, U36.10
unnamed: C142.2, R144.2
unnamed: JP257.1, R146.2
unnamed: JP257.3, R145.2
unnamed: C147.1, U37.12
unnamed: C146.1, U37.10
unnamed: C146.2, R148.2
unnamed: JP264.1, R150.2
unnamed: JP264.3, R149.2
unnamed: C151.1, U38.12
unnamed: C150.1, U38.10
unnamed: C150.2, R152.2
unnamed: JP271.1, R154.2
unnamed: JP271.3, R153.2
unnamed: C155.1, U39.12
unnamed: C154.1, U39.10
unnamed: C154.2, R156.2
unnamed: JP278.1, R158.2
unnamed: JP278.3, R157.2
unnamed: C159.1, U40.12
unnamed: C158.1, U40.10
unnamed: C158.2, R160.2
unnamed: JP285.1, R162.2
unnamed: JP285.3, R161.2
unnamed: C163.1, U41.12
unnamed: C162.1, U41.10
unnamed: C162.2, R164.2
unnamed: JP292.1, R166.2
unnamed: JP292.3, R165.2
unnamed: C167.1, U42.12
unnamed: C166.1, U42.10
unnamed: C166.2, R168.2
unnamed: JP299.1, R170.2
unnamed: JP299.3, R169.2
unnamed: C171.1, U43.12
unnamed: C170.1, U43.10
unnamed: C170.2, R172.2
unnamed: JP306.1, R174.2
unnamed: JP306.3, R173.2
unnamed: C175.1, U44.12
unnamed: C174.1, U44.10
unnamed: C174.2, R176.2
unnamed: JP313.1, R178.2
unnamed: JP313.3, R177.2
unnamed: C179.1, U45.12
unnamed: C178.1, U45.10
unnamed: C178.2, R180.2
unnamed: JP320.1, R182.2
unnamed: JP320.3, R181.2
unnamed: C183.1, U46.12
unnamed: C182.1, U46.10
unnamed: C182.2, R184.2
unnamed: JP327.1, R186.2
unnamed: JP327.3, R185.2
unnamed: C187.1, U47.12
unnamed: C186.1, U47.10
unnamed: C186.2, R188.2
unnamed: JP334.1, R190.2
unnamed: JP334.3, R189.2
unnamed: C191.1, U48.12
unnamed: C190.1, U48.10
unnamed: C190.2, R192.2
unnamed: JP341.1, R194.2
unnamed: JP341.3, R193.2
unnamed: C195.1, U49.12
unnamed: C194.1, U49.10
unnamed: C194.2, R196.2
unnamed: JP348.1, R198.2
unnamed: JP348.3, R197.2
unnamed: C199.1, U50.12
unnamed: C198.1, U50.10
unnamed: C198.2, R200.2
SCL: J2.4, J3.4, J4.4, R4.1, U2.3
SCL1: J5.4, J6.4, J7.4, R3.1, U1.3
SCL2: J9.4, J10.4, J11.4, R9.1, U3.3
SCL3: J13.4, J14.4, J15.4, R13.1, U4.3
SCL4: J17.4, J18.4, J19.4, R17.1, U5.3
SCL5: J21.4, J22.4, J23.4, R21.1, U6.3
SCL6: J25.4, J26.4, J27.4, R25.1, U7.3
SCL7: J29.4, J30.4, J31.4, R29.1, U8.3
SCL8: J33.4, J34.4, J35.4, R33.1, U9.3
SCL9: J37.4, J38.4, J39.4, R37.1, U10.3
SCL10: J41.4, J42.4, J43.4, R41.1, U11.3
SCL11: J45.4, J46.4, J47.4, R45.1, U12.3
SCL12: J49.4, J50.4, J51.4, R49.1, U13.3
SCL13: J53.4, J54.4, J55.4, R53.1, U14.3
SCL14: J57.4, J58.4, J59.4, R57.1, U15.3
SCL15: J61.4, J62.4, J63.4, R61.1, U16.3
SCL16: J65.4, J66.4, J67.4, R65.1, U17.3
SCL17: J69.4, J70.4, J71.4, R69.1, U18.3
SCL18: J73.4, J74.4, J75.4, R73.1, U19.3
SCL19: J77.4, J78.4, J79.4, R77.1, U20.3
SCL20: J81.4, J82.4, J83.4, R81.1, U21.3
SCL21: J85.4, J86.4, J87.4, R85.1, U22.3
SCL22: J89.4, J90.4, J91.4, R89.1, U23.3
SCL23: J93.4, J94.4, J95.4, R93.1, U24.3
SCL24: J97.4, J98.4, J99.4, R97.1, U25.3
SCL25: J101.4, J102.4, J103.4, R101.1, U26.3
SCL26: J105.4, J106.4, J107.4, R105.1, U27.3
SCL27: J109.4, J110.4, J111.4, R109.1, U28.3
SCL28: J113.4, J114.4, J115.4, R113.1, U29.3
SCL29: J117.4, J118.4, J119.4, R117.1, U30.3
SCL30: J121.4, J122.4, J123.4, R121.1, U31.3
SCL31: J125.4, J126.4, J127.4, R125.1, U32.3
SCL32: J129.4, J130.4, J131.4, R129.1, U33.3
SCL33: J133.4, J134.4, J135.4, R133.1, U34.3
SCL34: J137.4, J138.4, J139.4, R137.1, U35.3
SCL35: J141.4, J142.4, J143.4, R141.1, U36.3
SCL36: J145.4, J146.4, J147.4, R145.1, U37.3
SCL37: J149.4, J150.4, J151.4, R149.1, U38.3
SCL38: J153.4, J154.4, J155.4, R153.1, U39.3
SCL39: J157.4, J158.4, J159.4, R157.1, U40.3
SCL40: J161.4, J162.4, J163.4, R161.1, U41.3
SCL41: J165.4, J166.4, J167.4, R165.1, U42.3
SCL42: J169.4, J170.4, J171.4, R169.1, U43.3
SCL43: J173.4, J174.4, J175.4, R173.1, U44.3
SCL44: J177.4, J178.4, J179.4, R177.1, U45.3
SCL45: J181.4, J182.4, J183.4, R181.1, U46.3
SCL46: J185.4, J186.4, J187.4, R185.1, U47.3
SCL47: J189.4, J190.4, J191.4, R189.1, U48.3
SCL48: J193.4, J194.4, J195.4, R193.1, U49.3
SCL49: J197.4, J198.4, J199.4, R197.1, U50.3
SDA: J2.3, J3.3, J4.3, R5.1, U2.2
SDA1: J5.3, J6.3, J7.3, R6.1, U1.2
SDA2: J9.3, J10.3, J11.3, R10.1, U3.2
SDA3: J13.3, J14.3, J15.3, R14.1, U4.2
SDA4: J17.3, J18.3, J19.3, R18.1, U5.2
SDA5: J21.3, J22.3, J23.3, R22.1, U6.2
SDA6: J25.3, J26.3, J27.3, R26.1, U7.2
SDA7: J29.3, J30.3, J31.3, R30.1, U8.2
SDA8: J33.3, J34.3, J35.3, R34.1, U9.2
SDA9: J37.3, J38.3, J39.3, R38.1, U10.2
SDA10: J41.3, J42.3, J43.3, R42.1, U11.2
SDA11: J45.3, J46.3, J47.3, R46.1, U12.2
SDA12: J49.3, J50.3, J51.3, R50.1, U13.2
SDA13: J53.3, J54.3, J55.3, R54.1, U14.2
SDA14: J57.3, J58.3, J59.3, R58.1, U15.2
SDA15: J61.3, J62.3, J63.3, R62.1, U16.2
SDA16: J65.3, J66.3, J67.3, R66.1, U17.2
SDA17: J69.3, J70.3, J71.3, R70.1, U18.2
SDA18: J73.3, J74.3, J75.3, R74.1, U19.2
SDA19: J77.3, J78.3, J79.3, R78.1, U20.2
SDA20: J81.3, J82.3, J83.3, R82.1, U21.2
SDA21: J85.3, J86.3, J87.3, R86.1, U22.2
SDA22: J89.3, J90.3, J91.3, R90.1, U23.2
SDA23: J93.3, J94.3, J95.3, R94.1, U24.2
SDA24: J97.3, J98.3, J99.3, R98.1, U25.2
SDA25: J101.3, J102.3, J103.3, R102.1, U26.2
SDA26: J105.3, J106.3, J107.3, R106.1, U27.2
SDA27: J109.3, J110.3, J111.3, R110.1, U28.2
SDA28: J113.3, J114.3, J115.3, R114.1, U29.2
SDA29: J117.3, J118.3, J119.3, R118.1, U30.2
SDA30: J121.3, J122.3, J123.3, R122.1, U31.2
SDA31: J125.3, J126.3, J127.3, R126.1, U32.2
SDA32: J129.3, J130.3, J131.3, R130.1, U33.2
SDA33: J133.3, J134.3, J135.3, R134.1, U34.2
SDA34: J137.3, J138.3, J139.3, R138.1, U35.2
SDA35: J141.3, J142.3, J143.3, R142.1, U36.2
SDA36: J145.3, J146.3, J147.3, R146.1, U37.2
SDA37: J149.3, J150.3, J151.3, R150.1, U38.2
SDA38: J153.3, J154.3, J155.3, R154.1, U39.2
SDA39: J157.3, J158.3, J159.3, R158.1, U40.2
SDA40: J161.3, J162.3, J163.3, R162.1, U41.2
SDA41: J165.3, J166.3, J167.3, R166.1, U42.2
SDA42: J169.3, J170.3, J171.3, R170.1, U43.2
SDA43: J173.3, J174.3, J175.3, R174.1, U44.2
SDA44: J177.3, J178.3, J179.3, R178.1, U45.2
SDA45: J181.3, J182.3, J183.3, R182.1, U46.2
SDA46: J185.3, J186.3, J187.3, R186.1, U47.2
SDA47: J189.3, J190.3, J191.3, R190.1, U48.2
SDA48: J193.3, J194.3, J195.3, R194.1, U49.2
SDA49: J197.3, J198.3, J199.3, R198.1, U50.2

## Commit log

2018-02-16 checklist changes
2018-02-19 Post double check changes
2018-02-19 ordered protos
2018-02-20 updated i2c address
2018-03-07 post checklist changes
2018-03-09 moved to origin
2018-03-09 created panel v10

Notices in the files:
parts and their libraries:
SparkFun-Resistors: Licensing: Creative Commons ShareAlike 4.0 International - https://creativecommons.org/licenses/by-sa/4.0
SparkFun-Aesthetics: Released under the Creative Commons Attribution Share-Alike 4.0 License
SparkFun-Aesthetics: https://creativecommons.org/licenses/by-sa/4.0
